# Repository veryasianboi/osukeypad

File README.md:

Making an osu! keypad!!
All the KiCAD files are in here.

Parts: 
TBD!

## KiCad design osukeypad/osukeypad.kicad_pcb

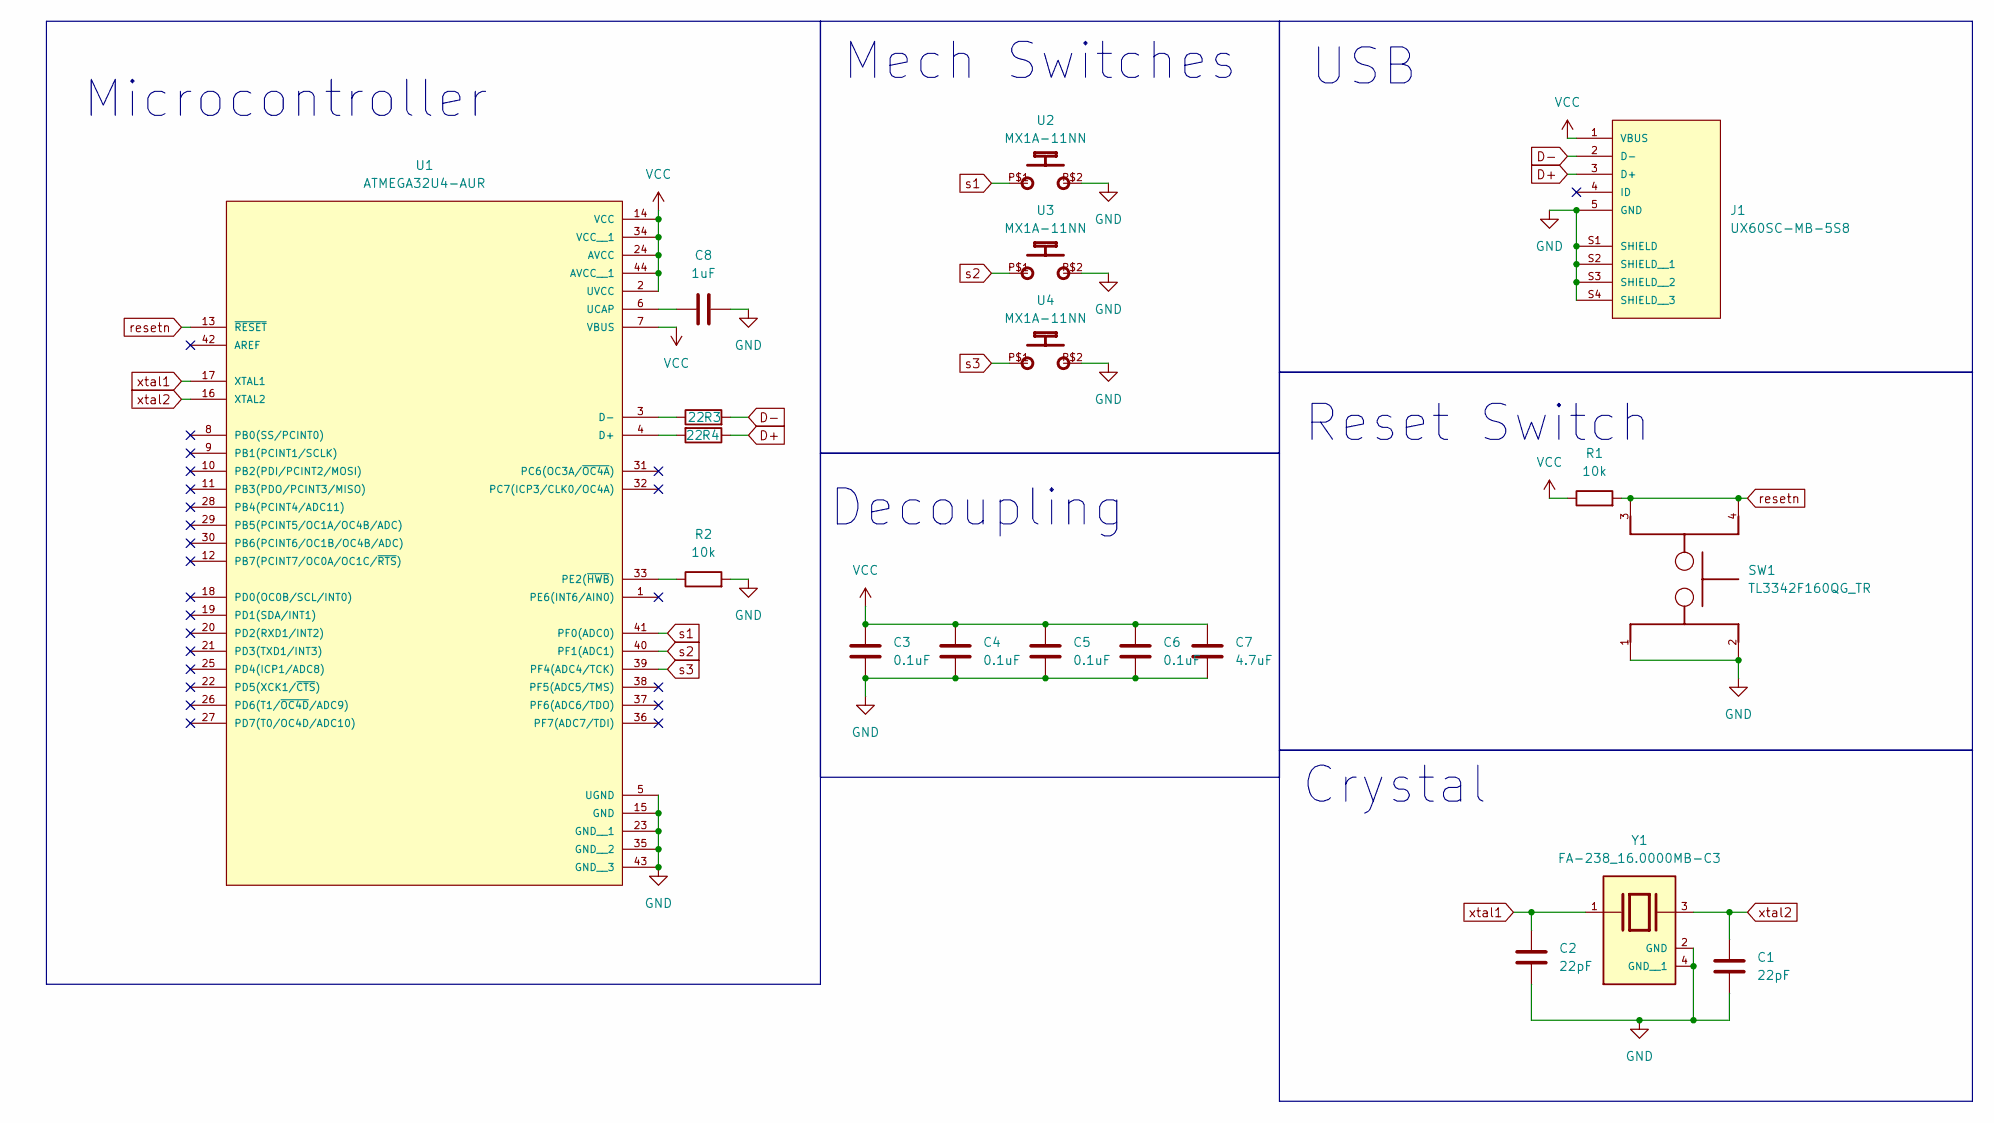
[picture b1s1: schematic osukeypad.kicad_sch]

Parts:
C1, C2: 22pF; C_0805_2012Metric_Pad1.18x1.45mm_HandSolder
C3, C4, C5, C6: 0.1uF; C_0805_2012Metric_Pad1.18x1.45mm_HandSolder
C7: 4.7uF; C_0805_2012Metric_Pad1.18x1.45mm_HandSolder
C8: 1uF; C_0805_2012Metric_Pad1.18x1.45mm_HandSolder
J1: UX60SC-MB-5S8; HIROSE_UX60SC-MB-5S8
R1, R2: 10k; R_0805_2012Metric_Pad1.20x1.40mm_HandSolder
R3, R4: 22; R_0805_2012Metric_Pad1.20x1.40mm_HandSolder
SW1: TL3342F160QG_TR; SW_TL3342F160QG_TR
U1: ATMEGA32U4-AUR; QFP80P1200X1200X120-44N
U2, U3, U4: MX1A-11NN; CHERRY_MX1A-11NN_SWITCH
Y1: FA-238_16.0000MB-C3; XTAL_FA-238_16.0000MB-C3; PARTREV N/A

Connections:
D+: J1.3 (D+), R4.1
D-: J1.2 (D-), R3.2
GND: C1.2, C2.2, C3.2, C4.2, C5.2, C6.2, C7.2, C8.2, J1.5 (GND), J1.S1 (SHIELD), J1.S2 (SHIELD__1), J1.S3 (SHIELD__2), J1.S4 (SHIELD__3), R2.2, SW1.1, SW1.2, U1.5 (UGND), U1.15 (GND), U1.23 (GND__1), U1.35 (GND__2), U1.43 (GND__3), U2.P$2, U3.P$2, U4.P$2, Y1.2 (GND), Y1.4 (GND__1)
unnamed: R4.2, U1.4 (D+)
unnamed: R3.1, U1.3 (D-)
unnamed: R2.1, U1.33 (PE2(~HWB))
unnamed: C8.1, U1.6 (UCAP)
VCC: C3.1, C4.1, C5.1, C6.1, C7.1, J1.1 (VBUS), R1.1, U1.2 (UVCC), U1.7 (VBUS), U1.14 (VCC), U1.24 (AVCC), U1.34 (VCC__1), U1.44 (AVCC__1)
resetn: R1.2, SW1.3, SW1.4, U1.13 (~RESET)
s1: U1.41 (PF0(ADC0)), U2.P$1
s2: U1.40 (PF1(ADC1)), U3.P$1
s3: U1.39 (PF4(ADC4/TCK)), U4.P$1
xtal1: C2.1, U1.17 (XTAL1), Y1.1
xtal2: C1.1, U1.16 (XTAL2), Y1.3

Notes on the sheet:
Microcontroller
Crystal
Decoupling
USB
Reset Switch
Mech Switches

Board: 2 copper layers, 19 parts (14 on the bottom side), 14 nets, no tracks yet.

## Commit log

2024-12-17 made the kicad file
2025-01-09 schematic done
